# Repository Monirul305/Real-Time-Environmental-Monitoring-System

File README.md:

# Real Time Environmental Monitoring System

**Creators: <br />
Monirul Islam, Dept of EEE, BUET <br />
Fariza Siddiqua, Dept of EEE, BUET <br />
A F M Mahfuzul Kabir, Dept of EEE, BUET <br />
Shuvro Chowdhury, Dept of EEE, BUET <br />**

**This project is for academic evaluation for EEE 416 course in Bangladesh University of Engineering and Technology (BUET).**

Environmental monitoring system using Arduino UNO. The system can sense air quality and temperature and humidly of a location and upload data to thingspeak. 
The system is charged automatically using solar power. The GSM network system uploads live data to server in real time.

The system uses Arduino UNO as the main controlling microprocessor. Three batteries are used for powering up the whole system. 
Two batteries are working in series to power the GSM module and sensors. The last battery is used to power up Arduino.
The GSM module draws high current while connecting to the network. A single battery can't suffice the current need for this system. So, batteeries are connected in
series to provide enough current.
Two charding modules are used to charge three batteries. Relays are used to switch the pararrel batteries to parallel when in charging mode. While discharging, the 
batteries are in series to provide enough power to the GSM. Since the battery output voltage is used while in series, voltage regulator is used so that the modules
are not harmed.

While in work, the system code defines the delay after which the system automatically goes into charging mode. For example, the system can be set to 5 minutes of charging
and then 2 minutes of discharging (fixed) in loop. During discharging, the system sends data from the sensors to the cloud.

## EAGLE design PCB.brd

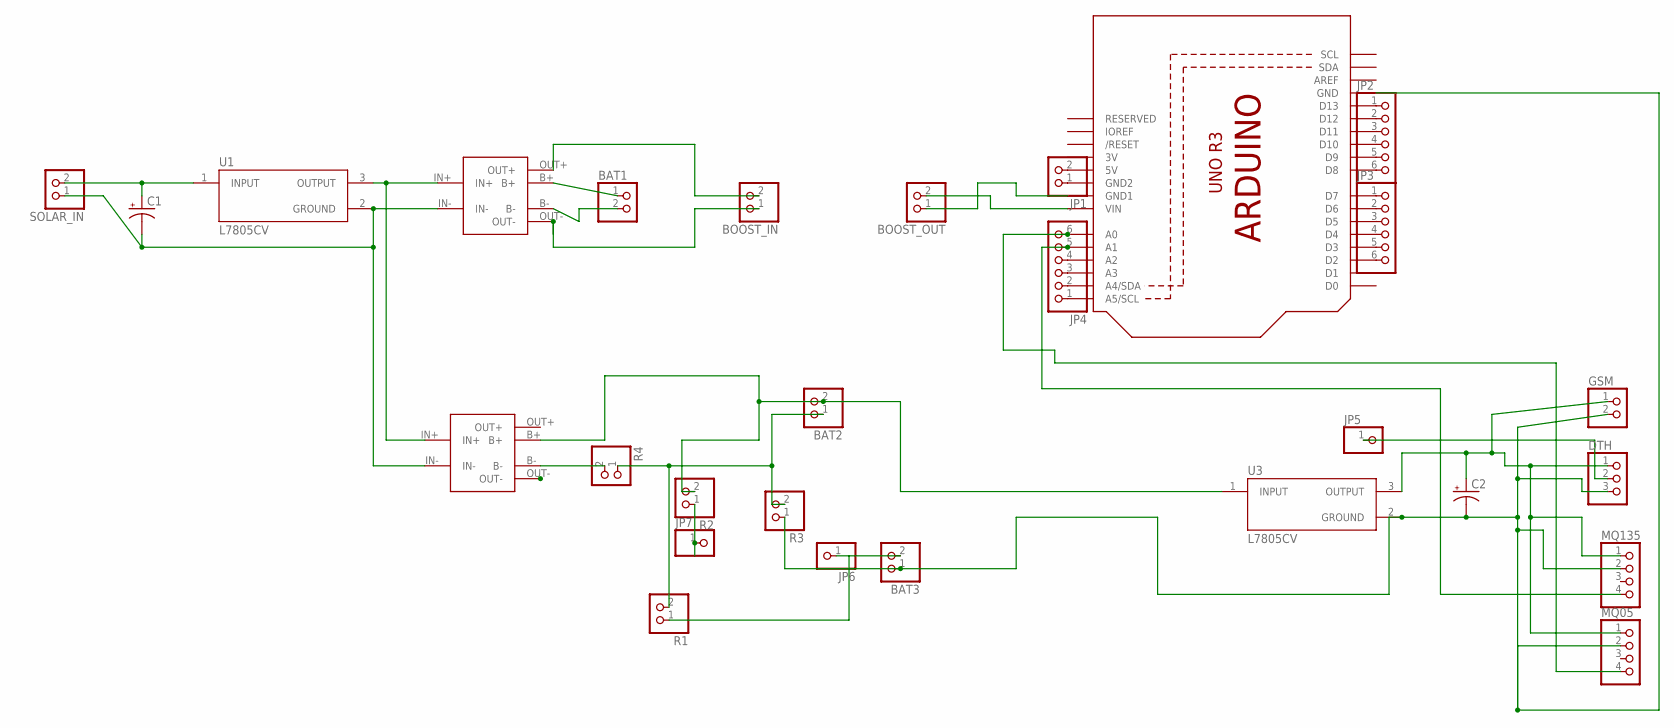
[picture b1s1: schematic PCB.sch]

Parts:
BAT1, BAT2, BAT3: PINHD-1X2; 1X02
BOOST_IN: PINHD-1X2; 1X02
BOOST_OUT: PINHD-1X2; 1X02
C1, C2: C-POL-US_RADIAL-11MM-DIA; CAPPRD508W65D1000H1100B
DTH: PINHD-1X3; 1X03
GSM: PINHD-1X2; 1X02
JP1: PINHD-1X2; 1X02
JP2, JP3, JP4: PINHD-1X6; 1X06
JP5, JP6, JP7: PINHD-1X1; 1X01
MQ05, MQ135: PINHD-1X4; 1X04
R1, R2, R3, R4: PINHD-1X2; 1X02
SOLAR_IN: PINHD-1X2; 1X02
U1, U3: L7805CV; TO255P1040X460X1968-3
U2: ARDUINOR3-DIMENSION; ARDUINOR3
U$3, U$5: TP4056-PTH

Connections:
3V: U2.3V
unnamed: U1.3 (OUTPUT), U$3.IN+, U$5.IN+
unnamed: C1.2 (-), SOLAR_IN.1, U1.2 (GROUND), U$3.IN-, U$5.IN-
unnamed: C1.1 (+), SOLAR_IN.2, U1.1 (INPUT)
unnamed: BAT1.1, U$3.B+
unnamed: BAT1.2, U$3.B-
unnamed: BOOST_IN.2, U$3.OUT+
unnamed: BOOST_IN.1, U$3.OUT-
unnamed: BOOST_OUT.2, U2.VIN
unnamed: BOOST_OUT.1, U2.GND1
unnamed: JP4.4, U2.A2
unnamed: R4.2, U$5.B-
unnamed: BAT2.1, R1.2, R3.2, R4.1
unnamed: BAT3.2, JP6.1
unnamed: DTH.2, JP5.1
unnamed: JP4.5, MQ135.4, U2.A1
unnamed: BAT3.1, C2.2 (-), DTH.3, GSM.2, MQ05.2, MQ135.2, R3.1, U2.GND, U3.2 (GROUND)
unnamed: C2.1 (+), DTH.1, GSM.1, MQ05.1, MQ135.1, U3.3 (OUTPUT)
unnamed: JP4.6, MQ05.4, U2.A0
unnamed: JP7.1, R2.1
unnamed: JP1.2, U2.5V
unnamed: JP1.1, U2.GND2
unnamed: BAT2.2, R2.2, U3.1 (INPUT), U$5.B+
unnamed: JP2.1, U2.D13
unnamed: JP2.2, U2.D12
unnamed: JP2.3, U2.D11
unnamed: JP2.4, U2.D10
unnamed: JP2.5, U2.D9
unnamed: JP2.6, U2.D8
unnamed: JP3.1, U2.D7
unnamed: JP3.2, U2.D6
unnamed: JP3.3, U2.D5
unnamed: JP3.4, U2.D4
unnamed: JP3.5, U2.D3
unnamed: JP3.6, U2.D2
unnamed: JP4.1, U2.A5 (A5/SCL)
unnamed: JP4.2, U2.A4 (A4/SDA)
unnamed: JP4.3, U2.A3

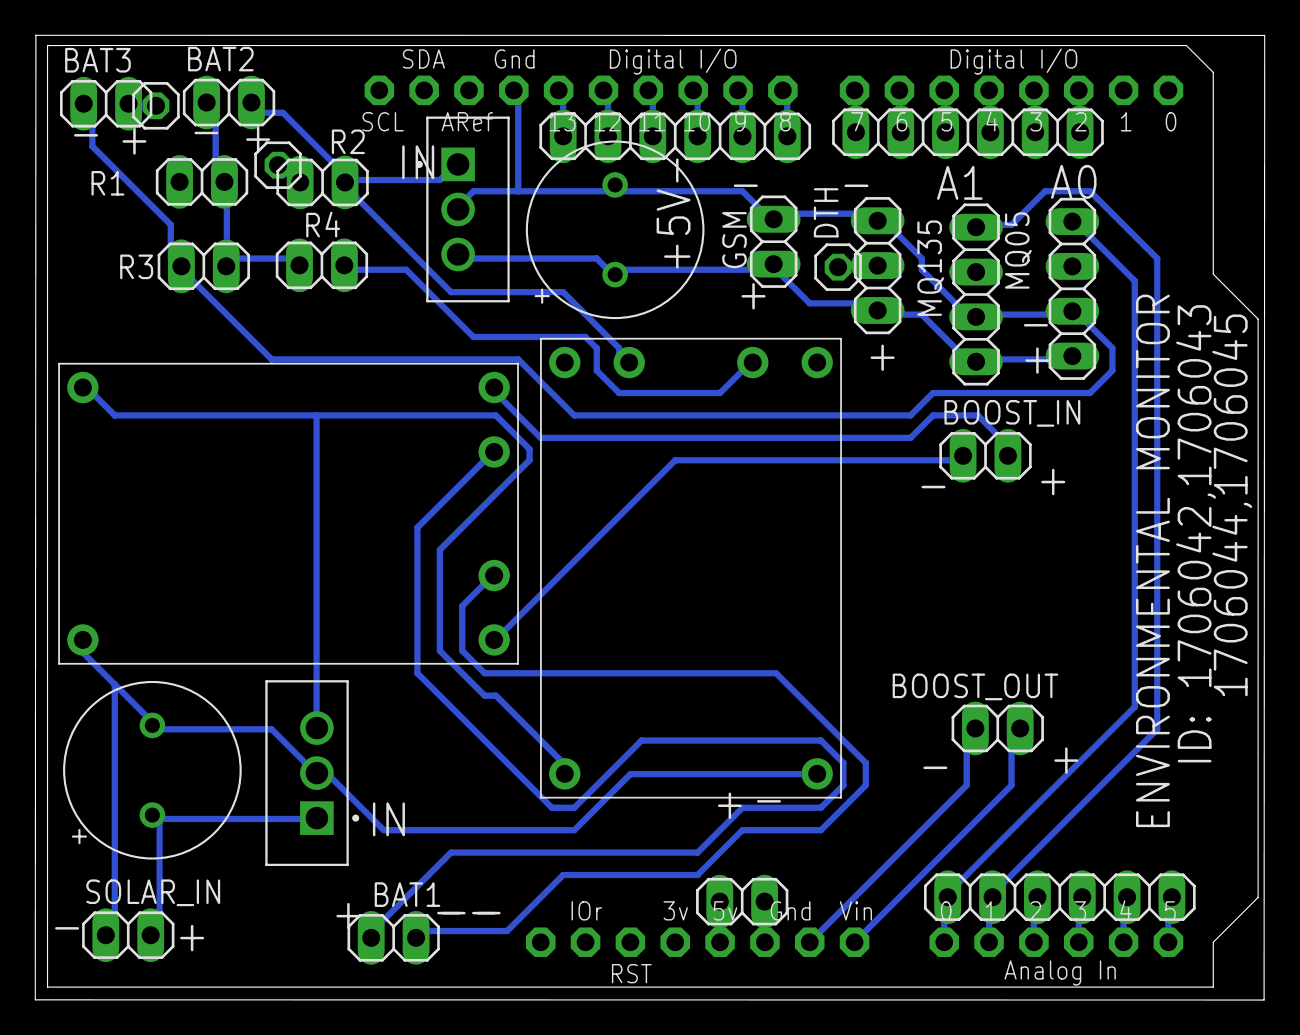
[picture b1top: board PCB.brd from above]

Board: 2 copper layers, 69.6 x 54.7 mm, 28 parts (0 on the bottom side), 37 nets.
